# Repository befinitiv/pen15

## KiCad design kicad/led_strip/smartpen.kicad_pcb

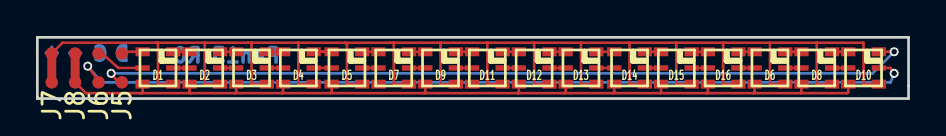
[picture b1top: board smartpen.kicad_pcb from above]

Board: 2 copper layers, 48.4 x 3.4 mm, 24 parts (0 on the bottom side), 36 nets.

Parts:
D1, D2, D3, D4, D5, D6, D7, D8, D9, D10, D11, D12, D13, D14, D15, D16: APA102; APA102-2020
J1: SDI; smallpad
J2: CKI; smallpad
J3: GND; smallpad
J4: VCC; smallpad
J5: SDO; smallpad
J6: CKO; smallpad
J7: VCCO; smallpad
J8: GNDO; smallpad

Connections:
unnamed: D1.1, D2.2
unnamed: D1.2, J1.1
unnamed: D1.3, J2.1
unnamed: D1.4, D2.4, D3.4, D4.4, D5.4, D6.4, D7.4, D8.4, D9.4, D10.4, D11.4, D12.4, D13.4, D14.4, D15.4, D16.4, J3.1, J8.1
unnamed: D1.5, D2.5, D3.5, D4.5, D5.5, D6.5, D7.5, D8.5, D9.5, D10.5, D11.5, D12.5, D13.5, D14.5, D15.5, D16.5, J4.1, J7.1
unnamed: D1.6, D2.3
unnamed: D2.1, D3.2
unnamed: D2.6, D3.3
unnamed: D3.1, D4.2
unnamed: D3.6, D4.3
unnamed: D4.1, D5.2
unnamed: D4.6, D5.3
unnamed: D5.1, D7.2
unnamed: D5.6, D7.3
unnamed: D6.1, D8.2
unnamed: D6.6, D8.3
unnamed: D7.1, D9.2
unnamed: D7.6, D9.3
unnamed: D10.1, J5.1
unnamed: D8.1, D10.2
unnamed: D8.6, D10.3
unnamed: D10.6, J6.1
unnamed: D11.1, D12.2
unnamed: D9.1, D11.2
unnamed: D9.6, D11.3
unnamed: D11.6, D12.3
unnamed: D12.1, D13.2
unnamed: D12.6, D13.3
unnamed: D13.1, D14.2
unnamed: D13.6, D14.3
unnamed: D14.1, D15.2
unnamed: D14.6, D15.3
unnamed: D15.1, D16.2
unnamed: D15.6, D16.3
unnamed: D6.2, D16.1
unnamed: D6.3, D16.6

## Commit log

2018-12-01 Added source code for raspberry pi
